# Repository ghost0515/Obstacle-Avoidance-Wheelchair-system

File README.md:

# Obstacle-Avoidance-Wheelchair-system
----
# Contributors
* Khang Nguyen
* Chamberlain Egbunike
* Vivian Obodo

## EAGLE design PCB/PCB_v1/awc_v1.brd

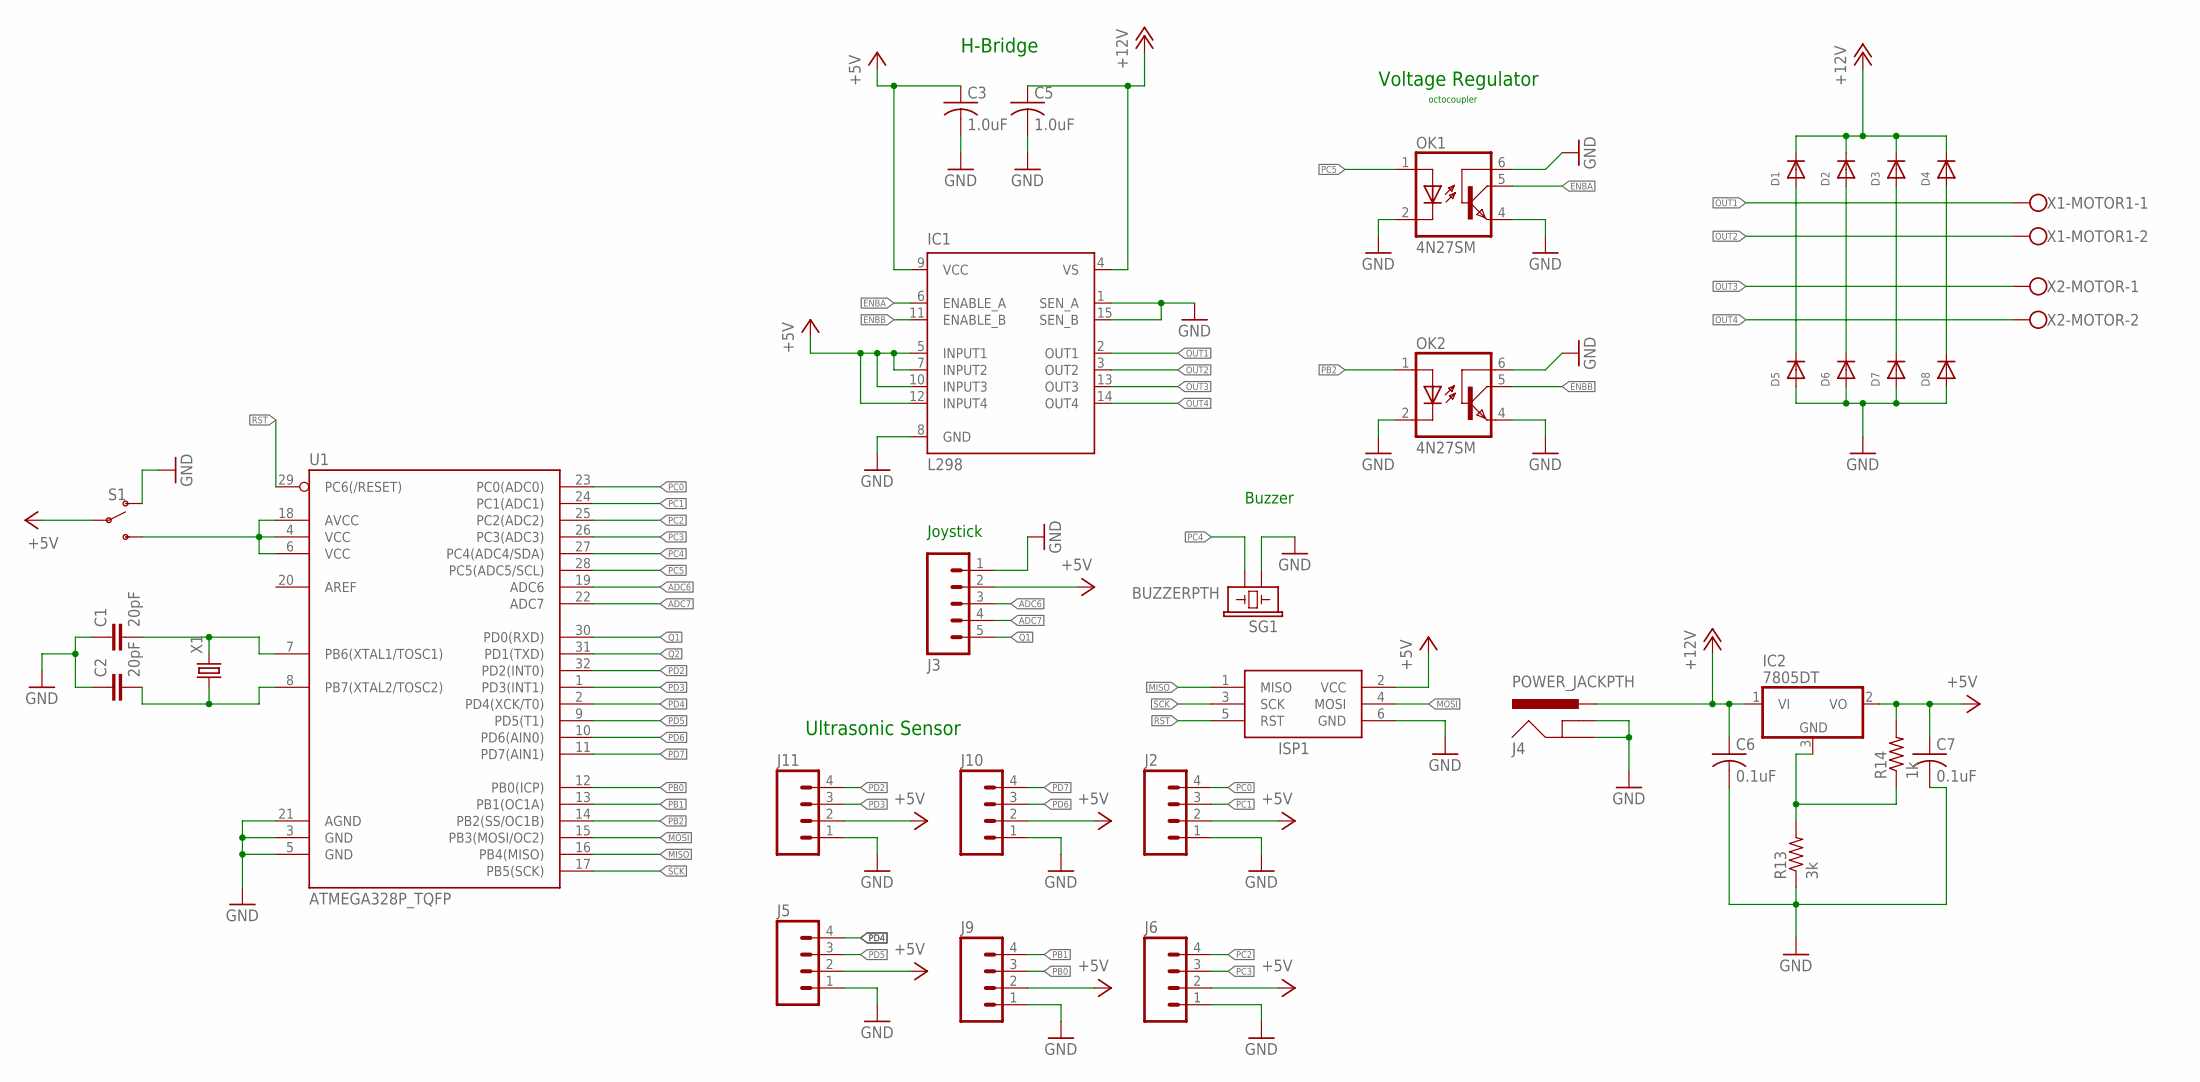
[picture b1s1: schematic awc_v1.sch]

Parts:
C1, C2: 20pF; C0805
C3, C5: 1.0uF; C0805
C6, C7: 0.1uF; C0805
D1, D2, D3, D4, D5, D6, D7, D8: DIODESOD-523; SOD-523
IC1: L298; MULTIWATT-15
IC2: 7805DT; TO252
ISP1: AVRISP-6; AVRISP
J2, J5, J6, J9, J10, J11: M04SCREW_LOCK; SCREWTERMINAL-3.5MM-4_LOCK
J3: M05SCREW; SCREWTERMINAL-3.5MM-5
J4: POWER_JACKPTH; POWER_JACK_PTH
OK1, OK2: 4N27SM; DIL6-SMD
R13: 3k; 0402-RES
R14: 1k; M0805
S1: SWITCH-SPDT-PTH-11.6X4.0MM; SWITCH_SPDT_PTH_11.6X4.0MM
SG1: BUZZERPTH; BUZZER-12MM
U1: ATMEGA328P_TQFP; TQFP32-08
X1: CRYSTALHC49UP; HC49UP
X1-MOTOR1, X2-MOTOR: W237-102

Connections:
+5V: C3.1, C7.1, IC1.5 (INPUT1), IC1.7 (INPUT2), IC1.9 (VCC), IC1.10 (INPUT3), IC1.12 (INPUT4), IC2.2 (VO), ISP1.2 (VCC), J2.2, J3.2, J5.2, J6.2, J9.2, J10.2, J11.2, R14.2, S1.2
+12V: C5.1, C6.1, D1.K (C), D2.K (C), D3.K (C), D4.K (C), IC1.4 (VS), IC2.1 (VI), J4.PWR
ADC6: J3.3, U1.19 (ADC6)
ADC7: J3.4, U1.22 (ADC7)
ENBA: IC1.6 (ENABLE_A), OK1.5 (COL)
ENBB: IC1.11 (ENABLE_B), OK2.5 (COL)
GND: C1.1, C2.1, C3.2, C5.2, C6.2, C7.2, D5.A, D6.A, D7.A, D8.A, IC1.1 (SEN_A), IC1.8 (GND), IC1.15 (SEN_B), ISP1.6 (GND), J2.1, J3.1, J4.GND, J4.GNDBREAK, J5.1, J6.1, J9.1, J10.1, J11.1, OK1.2 (C), OK1.4 (EMI), OK1.6 (BAS), OK2.2 (C), OK2.4 (EMI), OK2.6 (BAS), R13.1, S1.1 (O), SG1.+ (1), U1.3 (GND), U1.5 (GND), U1.21 (AGND)
MISO: ISP1.1 (MISO), U1.16 (PB4(MISO))
MOSI: ISP1.4 (MOSI), U1.15 (PB3(MOSI/OC2))
unnamed: D1.A, D5.K (C)
unnamed: D2.A, D6.K (C)
unnamed: D3.A, D7.K (C)
unnamed: D4.A, D8.K (C)
unnamed: C1.2, U1.7 (PB6(XTAL1/TOSC1)), X1.2
unnamed: C2.2, U1.8 (PB7(XTAL2/TOSC2)), X1.1
unnamed: IC2.3 (GND), R13.2, R14.1
unnamed: S1.3 (S), U1.4 (VCC), U1.6 (VCC), U1.18 (AVCC)
OUT1: IC1.2 (OUT1), X1-MOTOR1.1
OUT2: IC1.3 (OUT2), X1-MOTOR1.2
OUT3: IC1.13 (OUT3), X2-MOTOR.1
OUT4: IC1.14 (OUT4), X2-MOTOR.2
PB0: J9.3, U1.12 (PB0(ICP))
PB1: J9.4, U1.13 (PB1(OC1A))
PB2: OK2.1 (A), U1.14 (PB2(SS/OC1B))
PC0: J2.4, U1.23 (PC0(ADC0))
PC1: J2.3, U1.24 (PC1(ADC1))
PC2: J6.4, U1.25 (PC2(ADC2))
PC3: J6.3, U1.26 (PC3(ADC3))
PC4: SG1.- (2), U1.27 (PC4(ADC4/SDA))
PC5: OK1.1 (A), U1.28 (PC5(ADC5/SCL))
PD2: J11.4, U1.32 (PD2(INT0))
PD3: J11.3, U1.1 (PD3(INT1))
PD4: J5.4, U1.2 (PD4(XCK/T0))
PD5: J5.3, U1.9 (PD5(T1))
PD6: J10.3, U1.10 (PD6(AIN0))
PD7: J10.4, U1.11 (PD7(AIN1))
Q1: J3.5, U1.30 (PD0(RXD))
Q2: U1.31 (PD1(TXD))
RST: ISP1.5 (RST), U1.29 (PC6(/RESET))
SCK: ISP1.3 (SCK), U1.17 (PB5(SCK))

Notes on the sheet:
Joystick
Ultrasonic Sensor
Buzzer
Voltage Regulator
H-Bridge
octocoupler

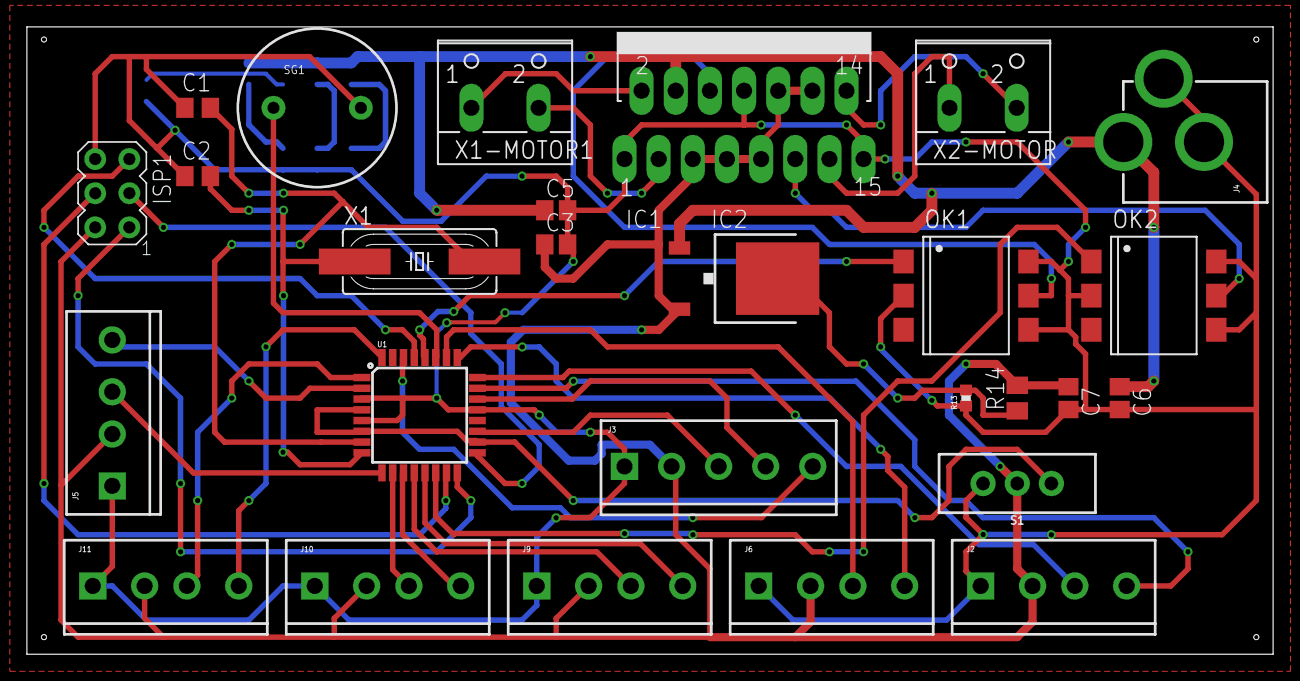
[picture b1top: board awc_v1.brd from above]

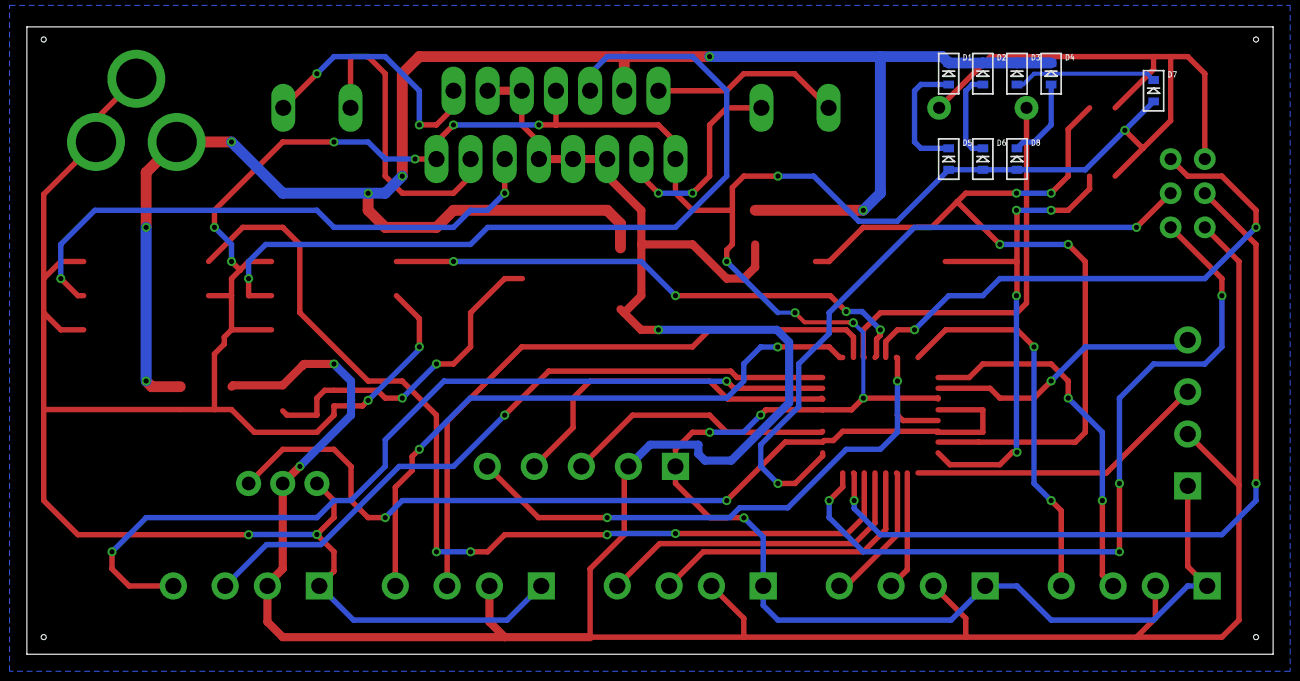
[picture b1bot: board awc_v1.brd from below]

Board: 2 copper layers, 92.7 x 46.7 mm, 35 parts (8 on the bottom side), 39 nets.

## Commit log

2017-11-03 git commit -m "Updated Firmware files"
2017-11-03 "Firmware v1"
2017-11-21 PCB design version 2
2017-11-21 PCB schematic and board v1

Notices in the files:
parts and their libraries:
SparkFun-Connectors: Licensing: Creative Commons ShareAlike 4.0 International - https://creativecommons.org/licenses/by-sa/4.0
